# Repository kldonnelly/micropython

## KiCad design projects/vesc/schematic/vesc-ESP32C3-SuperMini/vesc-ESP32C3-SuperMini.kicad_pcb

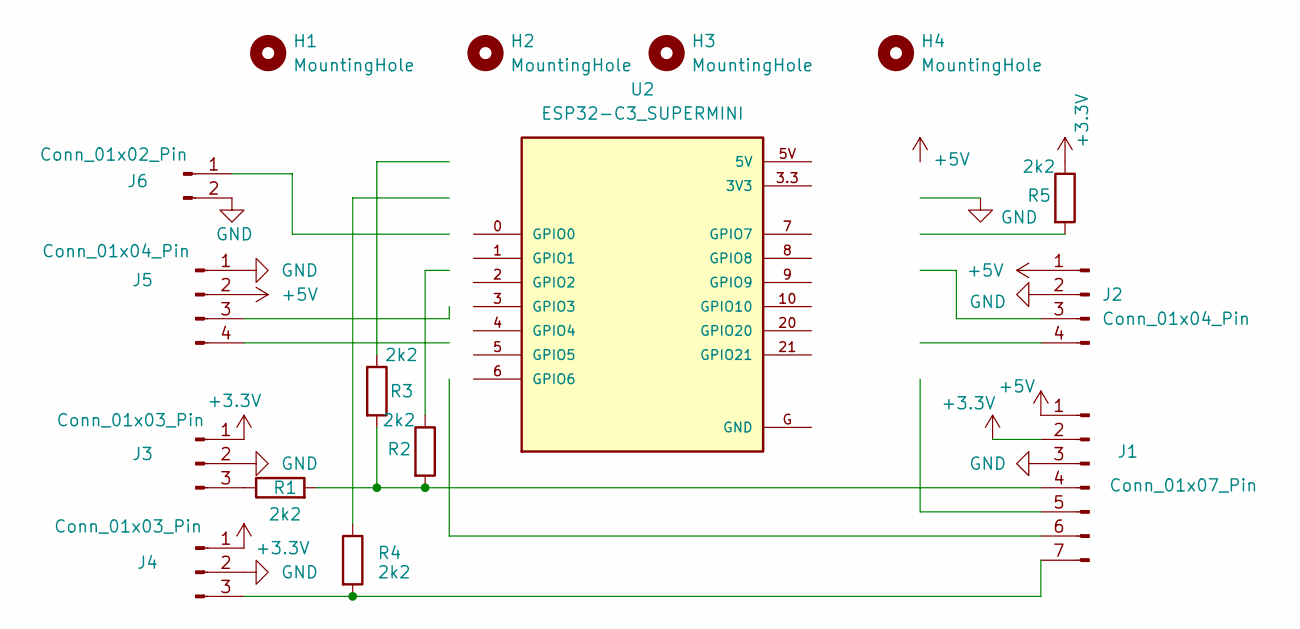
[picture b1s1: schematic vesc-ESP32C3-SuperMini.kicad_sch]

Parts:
H1, H2, H3, H4: MountingHole; MountingHole_2.2mm_M2
J1: Conn_01x07_Pin; JST_EH_B7B-EH-A_1x07_P2.50mm_Vertical
J2, J5: Conn_01x04_Pin; JST_EH_B4B-EH-A_1x04_P2.50mm_Vertical
J3, J4: Conn_01x03_Pin; JST_EH_B3B-EH-A_1x03_P2.50mm_Vertical
J6: Conn_01x02_Pin; JST_EH_B2B-EH-A_1x02_P2.50mm_Vertical
R1, R2, R3, R4, R5: 2k2; R_Axial_DIN0207_L6.3mm_D2.5mm_P10.16mm_Horizontal
U2: ESP32-C3_SUPERMINI; MODULE_ESP32-C3_SUPERMINI

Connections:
+3.3V: J1.2, J3.1, J4.1, R5.1
+5V: J1.1, J2.1, J5.2
GND: J1.3, J2.2, J3.2, J4.2, J5.1, J6.2
unnamed: J1.4, R1.2, R2.2, R3.2
unnamed: J1.7, J4.3, R4.2
unnamed: J3.3, R1.1

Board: 2 copper layers, 16 parts (0 on the bottom side), 6 nets, no tracks yet.

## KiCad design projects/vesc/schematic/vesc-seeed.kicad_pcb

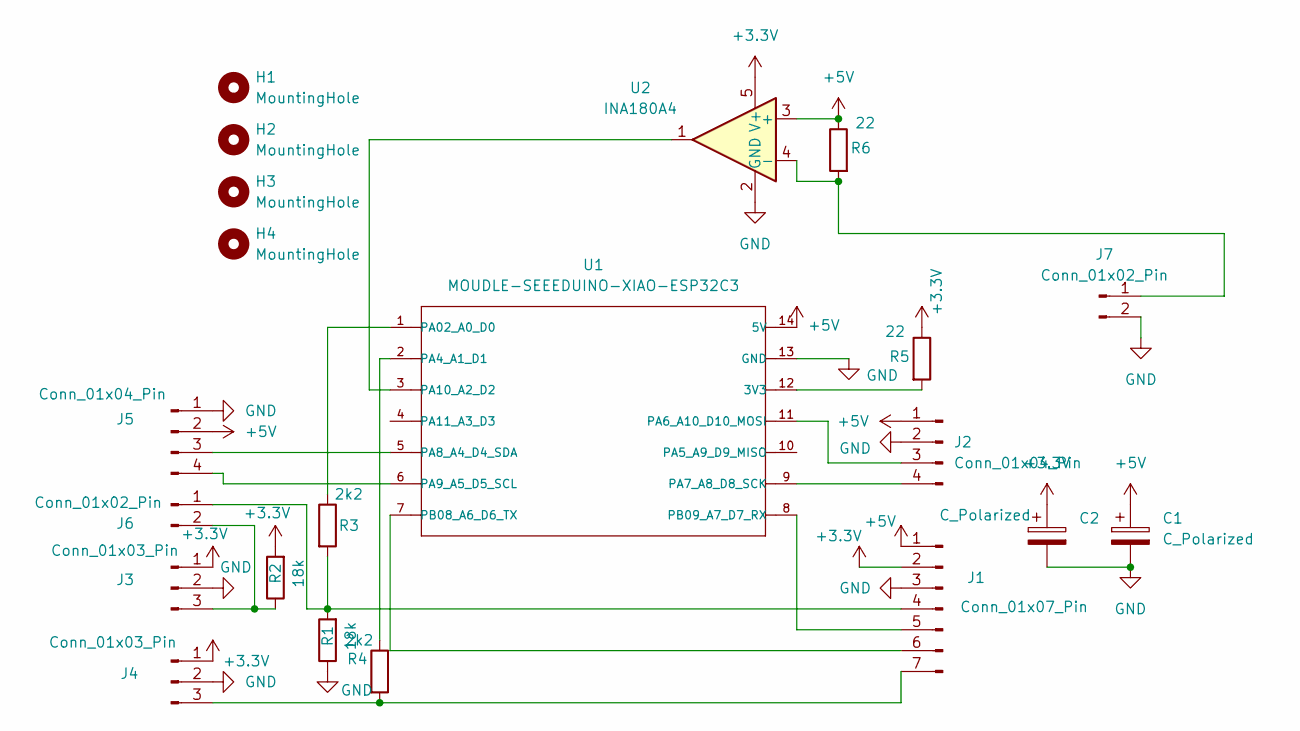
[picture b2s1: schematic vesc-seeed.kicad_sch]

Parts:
C1, C2: C_Polarized; CP_Radial_D8.0mm_P5.00mm
H1, H2, H3, H4: MountingHole; MountingHole_2.2mm_M2
J1: Conn_01x07_Pin; JST_EH_B7B-EH-A_1x07_P2.50mm_Vertical
J2, J5: Conn_01x04_Pin; JST_EH_B4B-EH-A_1x04_P2.50mm_Vertical
J3, J4: Conn_01x03_Pin; JST_EH_B3B-EH-A_1x03_P2.50mm_Vertical
J6, J7: Conn_01x02_Pin; JST_EH_B2B-EH-A_1x02_P2.50mm_Vertical
R1, R2: 18k; R_Axial_DIN0207_L6.3mm_D2.5mm_P10.16mm_Horizontal
R3, R4: 2k2; R_Axial_DIN0207_L6.3mm_D2.5mm_P10.16mm_Horizontal
R5, R6: 22; R_Axial_DIN0207_L6.3mm_D2.5mm_P10.16mm_Horizontal
U1: MOUDLE-SEEEDUINO-XIAO-ESP32C3; MOUDLE14P-SMD-2.54-21X17.8MM
U2: INA180A4; SOT-23-5

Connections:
+3.3V: C2.1, J1.2, J3.1, J4.1, R2.2, R5.1, U2.5 (V+)
+5V: C1.1, J1.1, J2.1, J5.2, R6.1, U1.14 (5V), U2.3 (+)
GND: C1.2, C2.2, J1.3, J2.2, J3.2, J4.2, J5.1, J7.2, R1.1, U1.13 (GND), U2.2 (GND)
unnamed: J1.4, J6.1, R1.2, R3.2
unnamed: J1.5, U1.8 (PB09_A7_D7_RX)
unnamed: J1.6, U1.7 (PB08_A6_D6_TX)
unnamed: J1.7, J4.3, R4.2
unnamed: J2.3, U1.11 (PA6_A10_D10_MOSI)
unnamed: J2.4, U1.9 (PA7_A8_D8_SCK)
unnamed: J3.3, J6.2, R2.1
unnamed: J5.3, U1.5 (PA8_A4_D4_SDA)
unnamed: J5.4, U1.6 (PA9_A5_D5_SCL)
unnamed: J7.1, R6.2, U2.4 (-)
unnamed: R5.2, U1.12 (3V3)
unnamed: R3.1, U1.1 (PA02_A0_D0)
unnamed: R4.1, U1.2 (PA4_A1_D1)
unnamed: U1.3 (PA10_A2_D2), U2.1

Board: 2 copper layers, 21 parts (0 on the bottom side), 17 nets, no tracks yet.

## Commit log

2022-05-03 pwm_audio
2024-05-04 micropyton-lib
2024-06-29 vesc schematic
